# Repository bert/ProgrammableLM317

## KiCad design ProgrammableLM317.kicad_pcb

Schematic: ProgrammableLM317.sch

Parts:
C1: 100uF
C2, C6: 10uF
C3, C4, C5, C7, C8, C9: 0.1uF
D1, D2: 1N4001
H1, H2, H3, H4: HOLE
IC1: ATTINY85-P; DIP8
K1: CONN_3
P1, P2, P3: CONN_2
R1: 10k
R2: 33k
R3: 220
R4: 100k
U1: LM317
U2: LM358
U3: MCP4801; DIP8
U4: 7805

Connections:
5V: C4.1, C6.1, C7.1, IC1.8 (VCC), R4.1, U2.5 (+), U3.1 (VDD), U3.6 (~SHDN~), U4.3 (OUT)
GND: C1.2, C2.2, C3.2, C4.2, C5.1, C6.2, C7.2, C8.2, C9.2, IC1.4 (GND), K1.3, P1.2 (PM), P2.2 (PM), P3.1, R1.2, U3.5 (~LDAC~), U3.7 (VSS), U4.2 (GND)
unnamed: IC1.6 (PB1(MISO/DO/AIN1/OC0B/OC1A/PCINT1)), U3.3 (SCK)
unnamed: IC1.7 (PB2(SCK/USCK/SCL/T0/INT0/ADC1/PCINT2)), U3.2 (~CS~)
unnamed: R1.1, R2.2, R4.2, U2.2 (-)
unnamed: D2.1 (A), R2.1, R3.2, U1.1 (ADJ), U2.1
unnamed: U2.6 (-), U2.7
unnamed: IC1.5 (PB0(MOSI/DI/SDA/AIN0/OC0A/OC1A/AREF/PCI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), U3.4 (SDI)
unnamed: U2.3 (+), U3.8 (Vout)
RX: IC1.2 (PB3(XTAL1/CLKI/OC1B/ADC3/PCINT3)), K1.1
TX: IC1.3 (PB4(XTAL2/CLKO/OC1B/ADC2/PCINT4)), K1.2 (PM)
Vcc: C1.1, C3.1, C8.1, D1.2 (K), P1.1, U1.3 (IN), U2.8 (V+), U4.1 (IN)
Vee: C5.2, P3.2 (PM), U2.4 (V-)
Vout: C2.1, C9.1, D1.1 (A), D2.2 (K), P2.1, R3.1, U1.2 (OUT)

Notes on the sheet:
Gain = 4.3
0V to 4.096V in 16mV steps
8-bit DAC in 4.096V mode 1 LSB = 16mV
0V to 17.613V in 69mV steps
1.25V to 18.863V in 69mV steps
RS-232 (TTL)
Safely terminating the unused op amp...

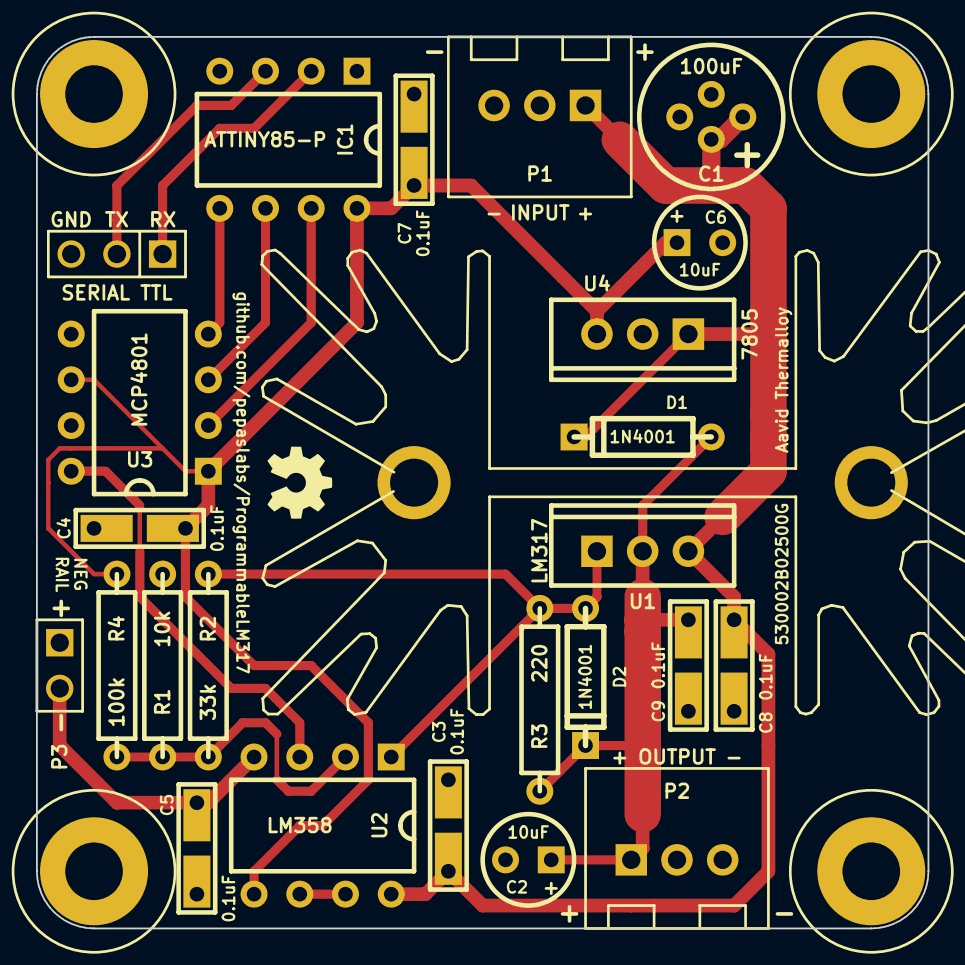
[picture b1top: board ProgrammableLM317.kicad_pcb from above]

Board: 2 copper layers, 49.5 x 49.5 mm, 29 parts (0 on the bottom side), 14 nets.

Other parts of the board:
H***: 530002B02500G

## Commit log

2015-04-08 all commands working. comments cleaned up.
2015-04-08 run-time verbosity configuration
2015-04-09 adding connector to supply negative rail to op amp.
2015-04-09 using multi-footprint for input and output connectors.
2015-04-09 using multi-footprints for ceramic bypass capacitors
2017-05-11 fixing a typo
